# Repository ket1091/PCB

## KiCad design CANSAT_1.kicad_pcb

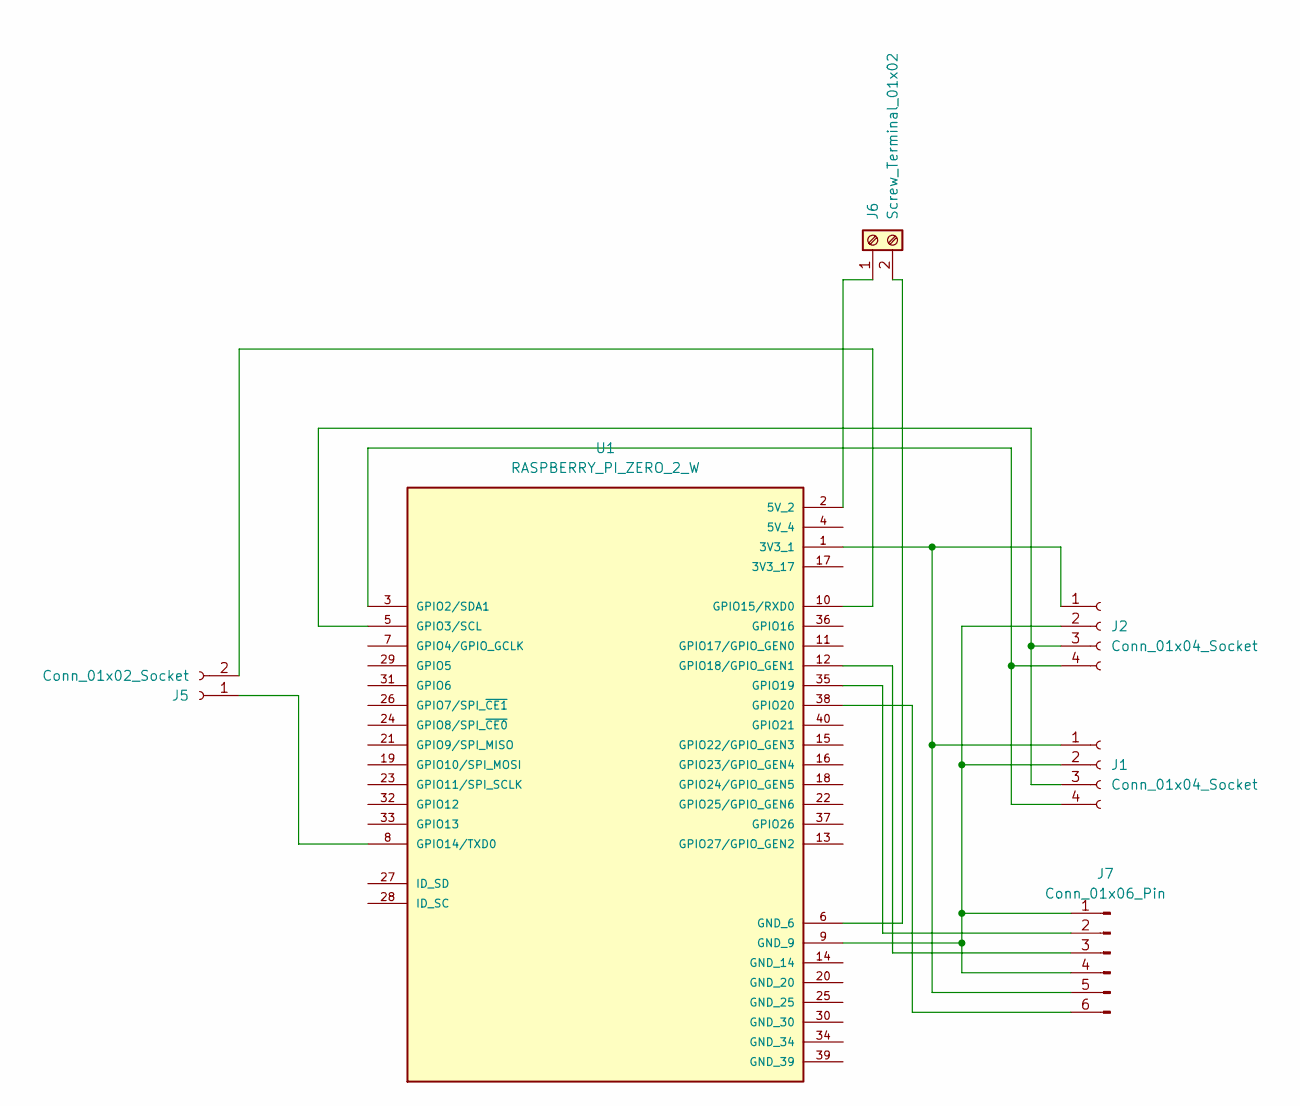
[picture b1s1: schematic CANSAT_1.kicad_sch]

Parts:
J1, J2: Conn_01x04_Socket; NS-Tech_Grove_1x04_P2mm_Vertical
J5: Conn_01x02_Socket; JWT_A3963_1x02_P3.96mm_Vertical
J6: Screw_Terminal_01x02; TerminalBlock_Altech_AK300-2_P5.00mm
J7: Conn_01x06_Pin; through hole 3-3
U1: RASPBERRY_PI_ZERO_2_W; MODULE_RASPBERRY_PI_ZERO_2_W; PARTREV April 2024

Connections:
unnamed: J1.1, J2.1, J7.5, U1.1 (3V3_1)
unnamed: J1.2, J2.2, J7.1, J7.4, U1.9 (GND_9)
unnamed: J1.3, J2.3, U1.5 (GPIO3/SCL)
unnamed: J1.4, J2.4, U1.3 (GPIO2/SDA1)
unnamed: J5.1, U1.8 (GPIO14/TXD0)
unnamed: J5.2, U1.10 (GPIO15/RXD0)
unnamed: J6.1, U1.2 (5V_2)
unnamed: J6.2, U1.6 (GND_6)
unnamed: J7.2, U1.35 (GPIO19)
unnamed: J7.3, U1.12 (GPIO18/GPIO_GEN1)
unnamed: J7.6, U1.38 (GPIO20)

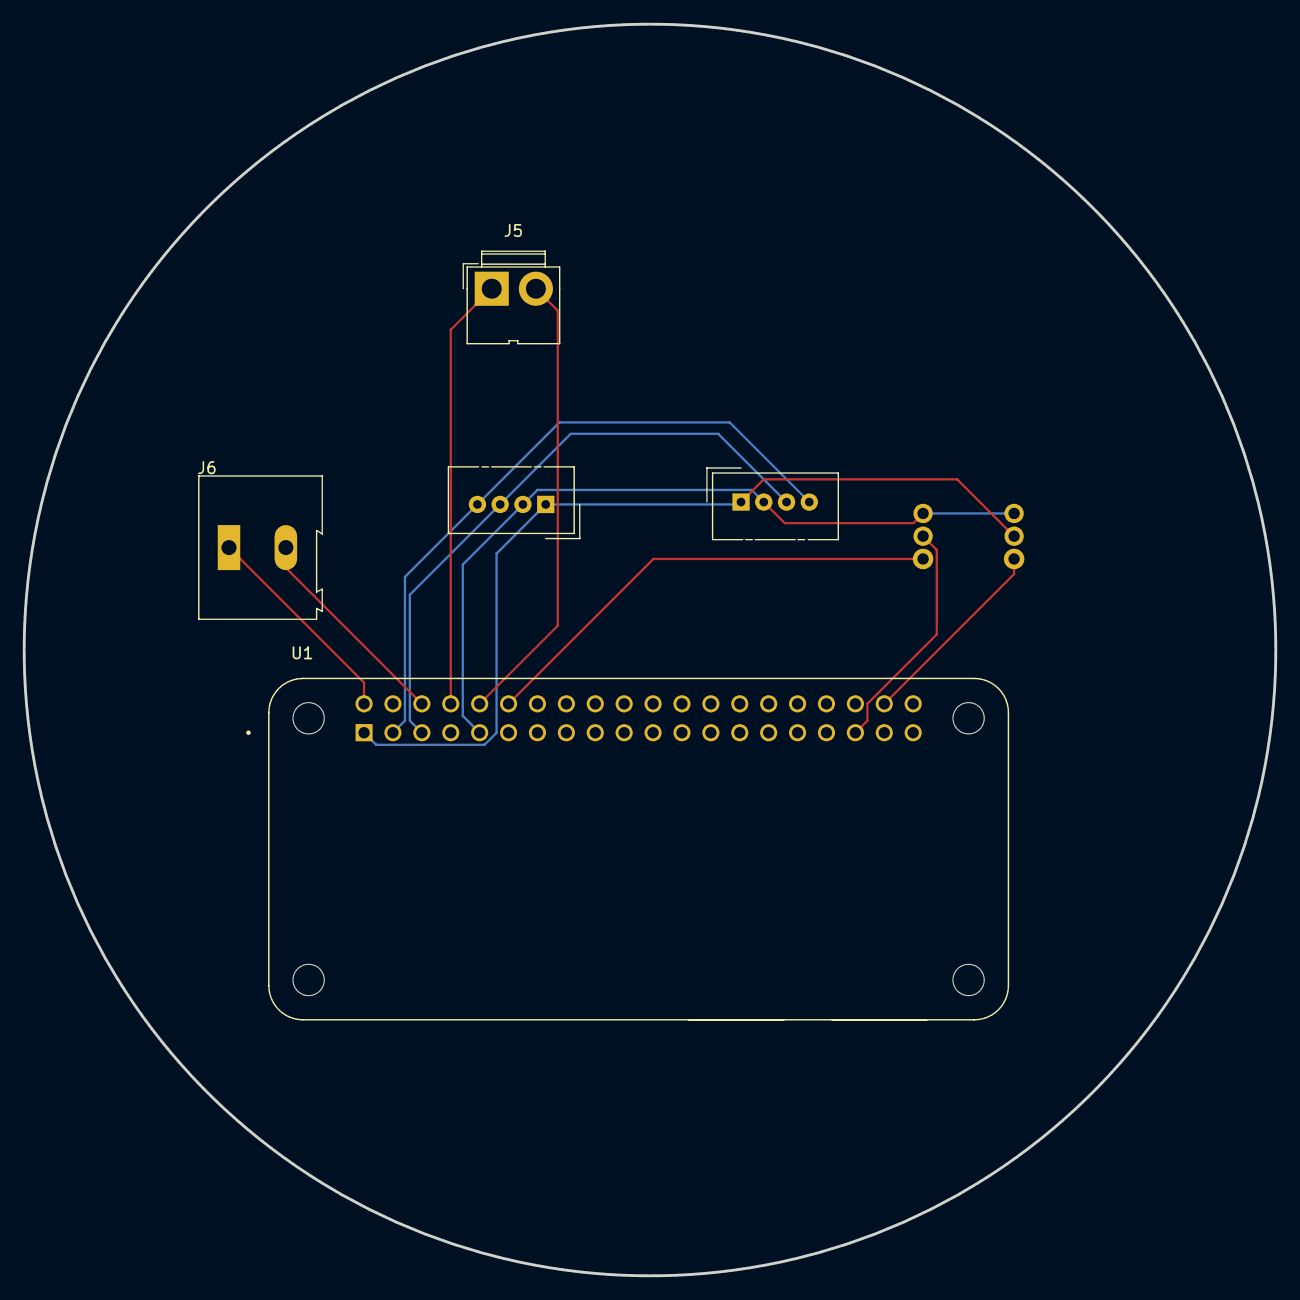
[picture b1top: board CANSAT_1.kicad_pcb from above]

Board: 2 copper layers, 110.0 x 110.0 mm, 6 parts (0 on the bottom side), 11 nets.

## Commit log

2025-09-02 Version 1
